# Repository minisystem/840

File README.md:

SYSTEM80 840
======================================

Voltage controlled ADSR in Eurorack format. Currently under development.

Hardware design by Minisystem: info@system80.net

LICENSE
=======
cc by-nc-sa
https://creativecommons.org/licenses/by-nc-sa/4.0/

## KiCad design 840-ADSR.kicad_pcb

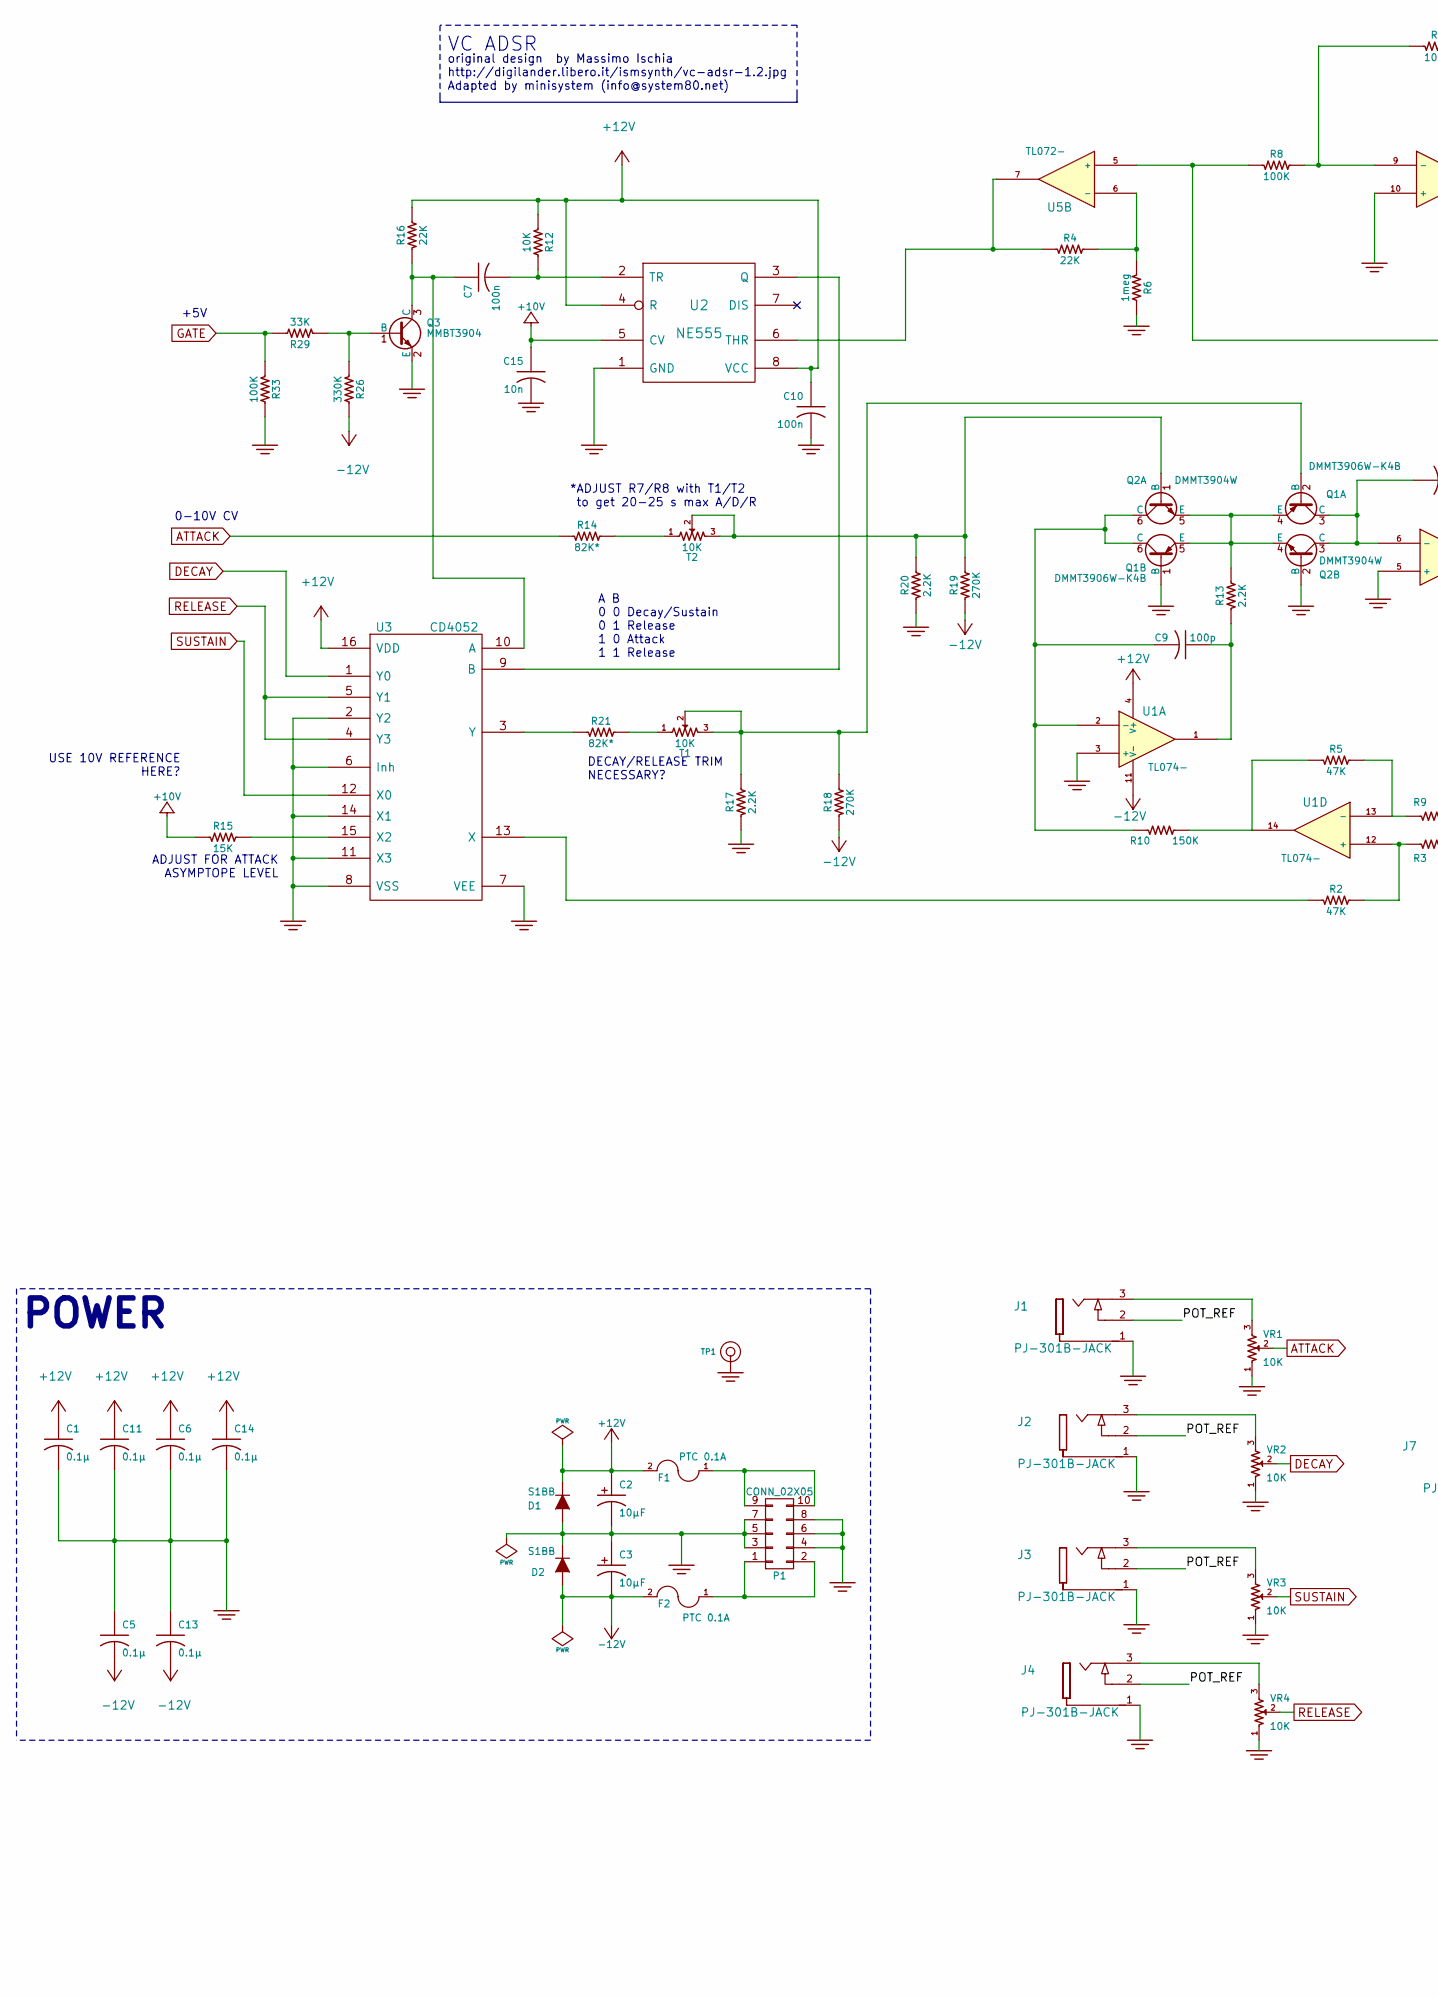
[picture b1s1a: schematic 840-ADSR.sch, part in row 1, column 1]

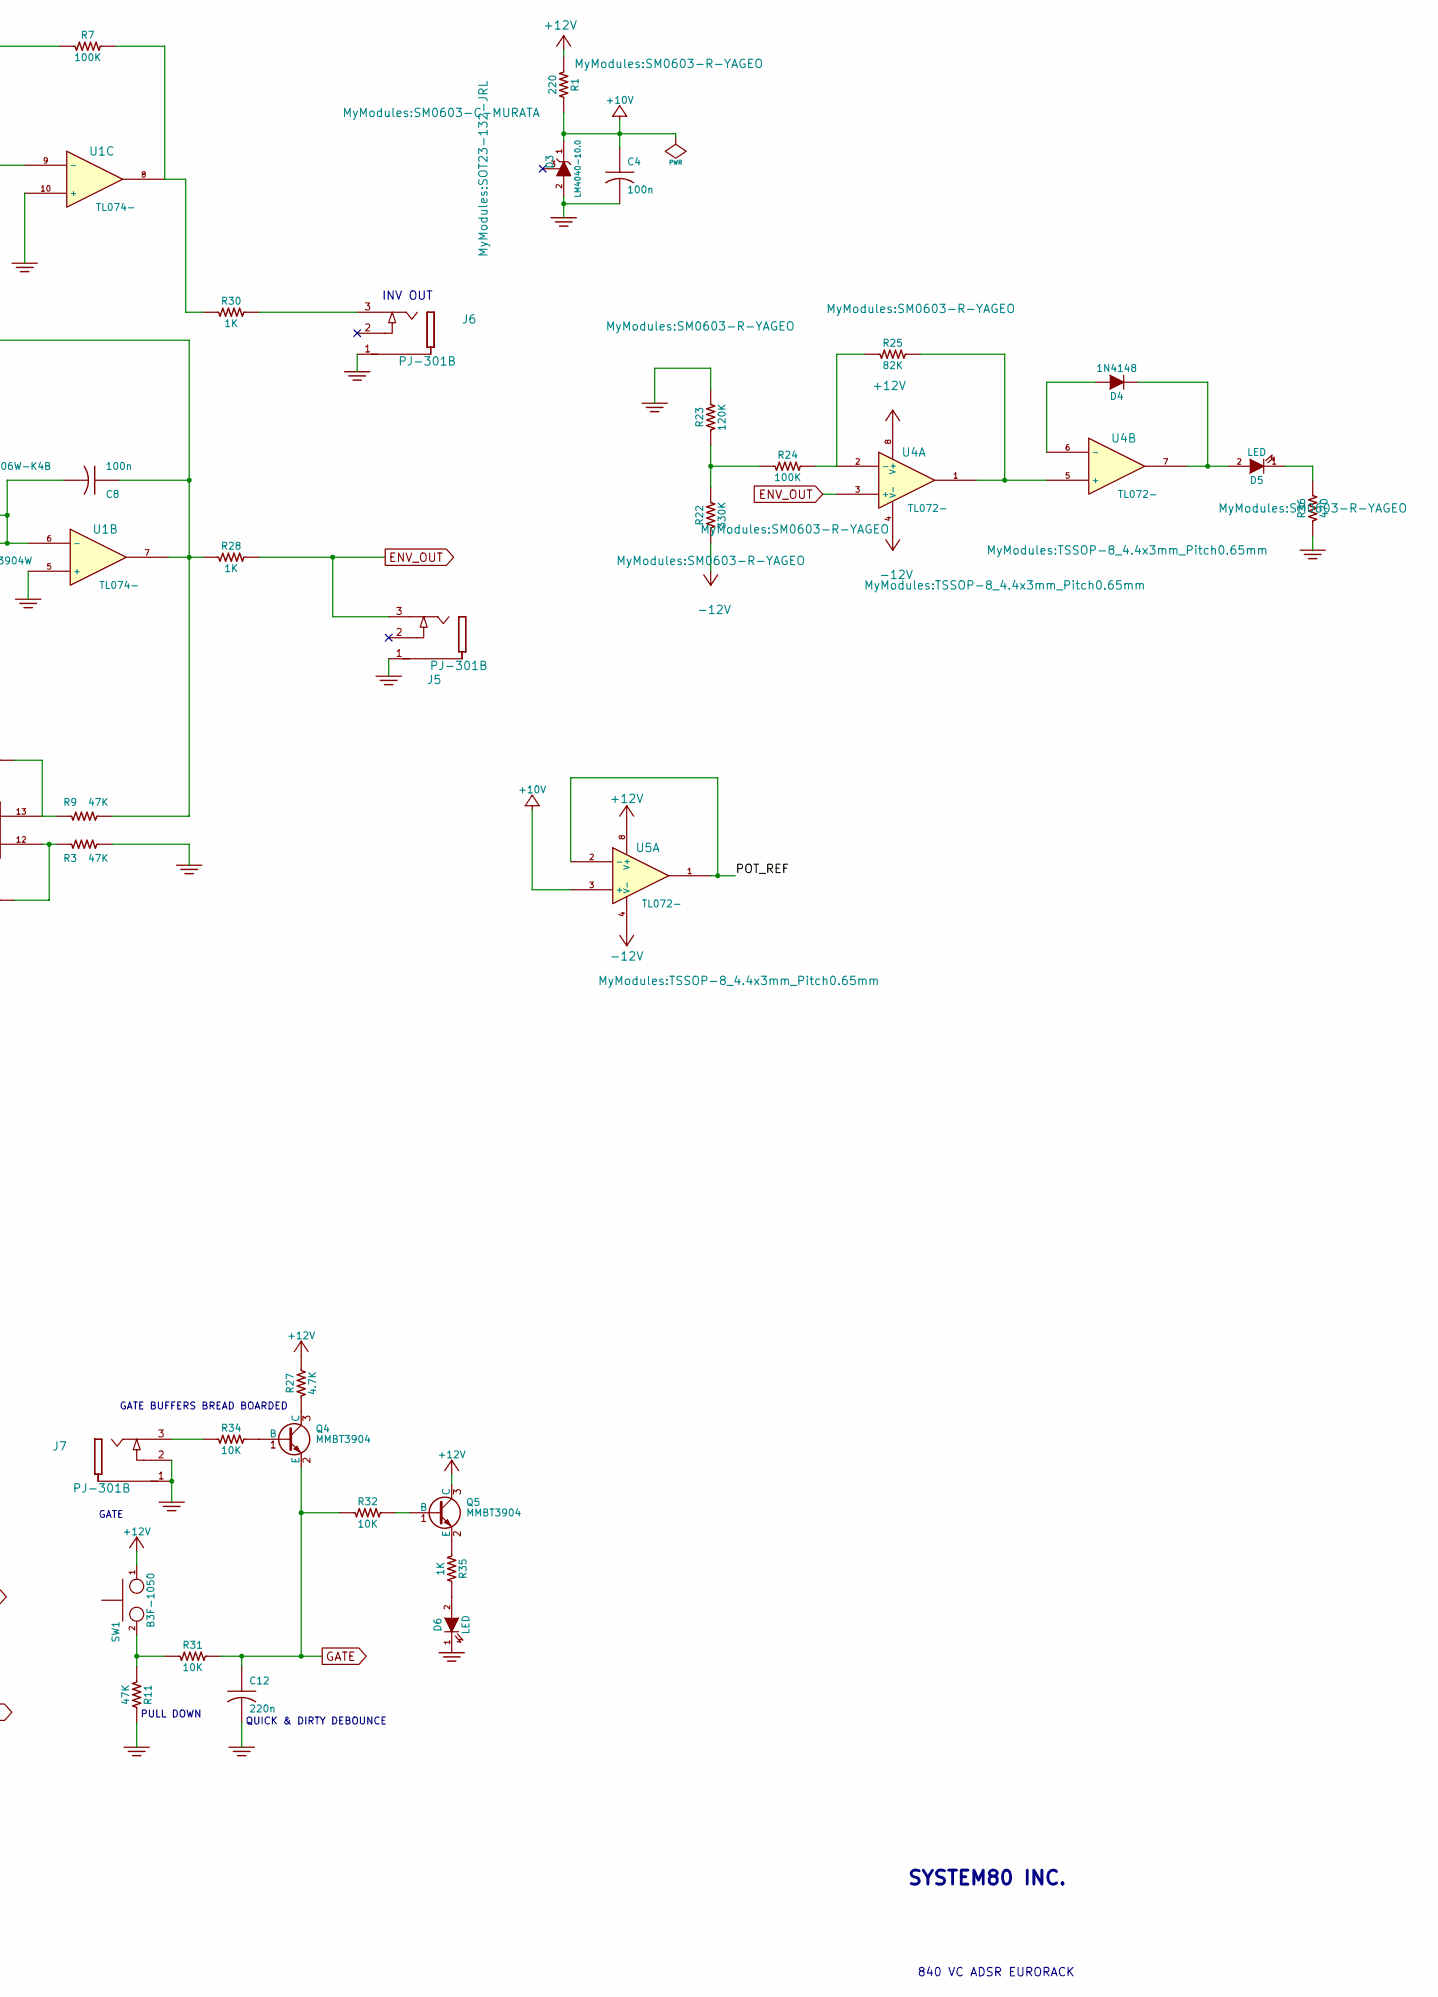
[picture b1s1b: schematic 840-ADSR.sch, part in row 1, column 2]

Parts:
C1, C5, C6, C11, C13, C14: 0.1µ; SM0603-C-MURATA
C2, C3: 10μF; jrl_c_elec_5x5.3
C4, C7, C8, C10: 100n; SM0603-C-MURATA
C9: 100p; SM0603-C-MURATA
C12: 220n; SM0805-HAND
C15: 10n; SM0603-C-MURATA
D1, D2: S1BB; SMB-1C2A
D3: LM4040-10.0; SOT23-132-JRL
D4: 1N4148; SOD323-C1A2
D5, D6: LED; 3MM-LED-C1A2
F1, F2: PTC 0.1A; SM0805-HAND
J1, J2, J3, J4: PJ-301B-JACK; PJ-301B-JACK-SLOTS
J5, J6, J7: PJ-301B; PJ-301B-JACK-SLOTS
P1: CONN_02X05; Pin_Header_Straight_2x05_Pitch2.54mm
Q1: DMMT3906W-K4B; SOT363-JRL
Q2: DMMT3904W; SOT363-JRL
Q3, Q4, Q5: MMBT3904; SOT23-132-JRL
R1: 220; SM0603-R-YAGEO
R2, R3, R5, R9, R11: 47K; SM0603-R-YAGEO
R4, R16: 22K; SM0603-R-YAGEO
R6: 1meg; SM0603-R-YAGEO
R7, R8, R24, R33: 100K; SM0603-R-YAGEO
R10: 150K; SM0603-R-YAGEO
R12, R31, R32, R34: 10K; SM0603-R-YAGEO
R13, R17, R20: 2.2K; SM0603-R-YAGEO
R14, R21: 82K*; SM0603-R-YAGEO
R15: 15K; SM0603-R-YAGEO
R18, R19: 270K; SM0603-R-YAGEO
R22, R26: 330K; SM0603-R-YAGEO
R23: 120K; SM0603-R-YAGEO
R25: 82K; SM0603-R-YAGEO
R27: 4.7K; SM0603-R-YAGEO
R28, R30, R35: 1K; SM0603-R-YAGEO
R29: 33K; SM0603-R-YAGEO
R36: 470; SM0603-R-YAGEO
SW1: B3F-1050; B3F-1050-OMRON
T1, T2: 10K; TC33X-2
TP1: CONN_1; TEST_POINT_LOOP_4592
U1: TL074-; TSSOP-14_4.4x5mm_Pitch0.65mm
U2: NE555; TSSOP-8_4.4x3mm_Pitch0.65mm
U3: CD4052; TSSOP-16_4.4x5mm_Pitch0.65mm_jrl
U4, U5: TL072-; TSSOP-8_4.4x3mm_Pitch0.65mm
VR1, VR2, VR3, VR4: 10K; RD901F-ALPHA-POT-T18

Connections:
+10V: C4.1, C15.1, D3.1 (K), R1.2, R15.1, U2.5 (CV), U5.3 (+)
+12V: C1.1, C2.1 (+), C6.1, C10.1, C11.1, C14.1, D1.1 (K), F1.2, Q5.3 (C), R1.1, R12.1, R16.2, R27.2, SW1.1, U1.4 (V+), U2.4 (R), U2.8 (VCC), U3.16 (VDD), U4.8 (V+), U5.8 (V+)
-12V: C3.2 (-), C5.2, C13.2, D2.2 (A), F2.2, R18.1, R19.1, R22.1, R26.2, U1.11 (V-), U4.4 (V-), U5.4 (V-)
/POT_REF: J1.2, J2.2, J3.2, J4.2, U5.1, U5.2 (-)
ATTACK: R14.1, VR1.2
DECAY: U3.1 (Y0), VR2.2
ENV_OUT: J5.3, R28.2, U4.3 (+)
GATE: C12.1, Q4.2 (E), R29.2, R31.2, R32.1, R33.1
GND: C1.2, C2.2 (-), C3.1 (+), C4.2, C5.1, C6.2, C10.2, C11.2, C12.2, C13.1, C14.2, C15.2, D1.2 (A), D2.1 (K), D3.2 (A), D6.1 (K), J1.1, J2.1, J3.1, J4.1, J5.1, J6.1, J7.1, J7.2, P1.3, P1.4, P1.5, P1.6, P1.7, P1.8, Q1.1 (B), Q2.2 (B), Q3.2 (E), R3.2, R6.2, R11.2, R17.1, R20.1, R23.2, R33.2, R36.1, TP1.1, U1.3 (+), U1.5 (+), U1.10 (+), U2.1 (GND), U3.2 (Y2), U3.6 (Inh), U3.7 (VEE), U3.8 (VSS), U3.11 (X3), U3.14 (X1), VR1.1, VR2.1, VR3.1, VR4.1
unnamed: C7.1, Q3.3 (C), R16.1, U3.10 (A)
unnamed: C7.2, R12.2, U2.2 (TR)
unnamed: C8.1, R8.1, R9.2, R28.1, U1.7, U5.5 (+)
unnamed: C8.2, Q1.3 (C), Q2.3 (C), U1.6 (-)
unnamed: C9.1, R13.1, U1.1
unnamed: C9.2, Q1.6 (C), Q2.6 (C), R10.1, U1.2 (-)
unnamed: D4.1 (K), D5.2 (A), U4.7
unnamed: D4.2 (A), U4.6 (-)
unnamed: D5.1 (K), R36.2
unnamed: D6.2 (A), R35.2
unnamed: F1.1, P1.9, P1.10
unnamed: F2.1, P1.1, P1.2
unnamed: J1.3, VR1.3
unnamed: J2.3, VR2.3
unnamed: J3.3, VR3.3
unnamed: J4.3, VR4.3
unnamed: J6.3, R30.2
unnamed: J7.3, R34.1
unnamed: Q1.2 (B), R17.2, R18.2, T1.2, T1.3
unnamed: Q1.4 (E), Q1.5 (E), Q2.4 (E), Q2.5 (E), R13.2
unnamed: Q2.1 (B), R19.2, R20.2, T2.2, T2.3
unnamed: Q3.1 (B), R26.1, R29.1
unnamed: Q4.1 (B), R34.2
unnamed: Q4.3 (C), R27.1
unnamed: Q5.1 (B), R32.2
unnamed: Q5.2 (E), R35.1
unnamed: R2.1, U3.13 (X)
unnamed: R2.2, R3.1, U1.12 (+)
unnamed: R4.1, U2.6 (THR), U5.7
unnamed: R4.2, R6.1, U5.6 (-)
unnamed: R5.2, R9.1, U1.13 (-)
unnamed: R7.1, R8.2, U1.9 (-)
unnamed: R5.1, R10.2, U1.14
unnamed: R11.1, R31.1, SW1.2
unnamed: R14.2, T2.1
unnamed: R15.2, U3.15 (X2)
unnamed: R21.1, U3.3 (Y)
unnamed: R21.2, T1.1
unnamed: R22.2, R23.1, R24.1
unnamed: R24.2, R25.1, U4.2 (-)
unnamed: R25.2, U4.1, U4.5 (+)
unnamed: R7.2, R30.1, U1.8
unnamed: U2.3 (Q), U3.9 (B)
RELEASE: U3.4 (Y3), U3.5 (Y1), VR4.2
SUSTAIN: U3.12 (X0), VR3.2

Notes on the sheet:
SYSTEM80 INC.
840 VC ADSR EURORACK
*ADJUST R7/R8 with T1/T2 to get 20-25 s max A/D/R
0-10V CV
+5V
VC ADSR
original design by Massimo Ischia http://digilander.libero.it/ismsynth/vc-adsr-1.2.jpg Adapted by minisystem (info@system80.net)
POWER
GATE
GATE BUFFERS BREAD BOARDED
QUICK & DIRTY DEBOUNCE
INV OUT
A B 0 0 Decay/Sustain 0 1 Release 1 0 Attack 1 1 Release
DECAY/RELEASE TRIM NECESSARY?
PULL DOWN
ADJUST FOR ATTACK ASYMPTOPE LEVEL
USE 10V REFERENCE HERE?

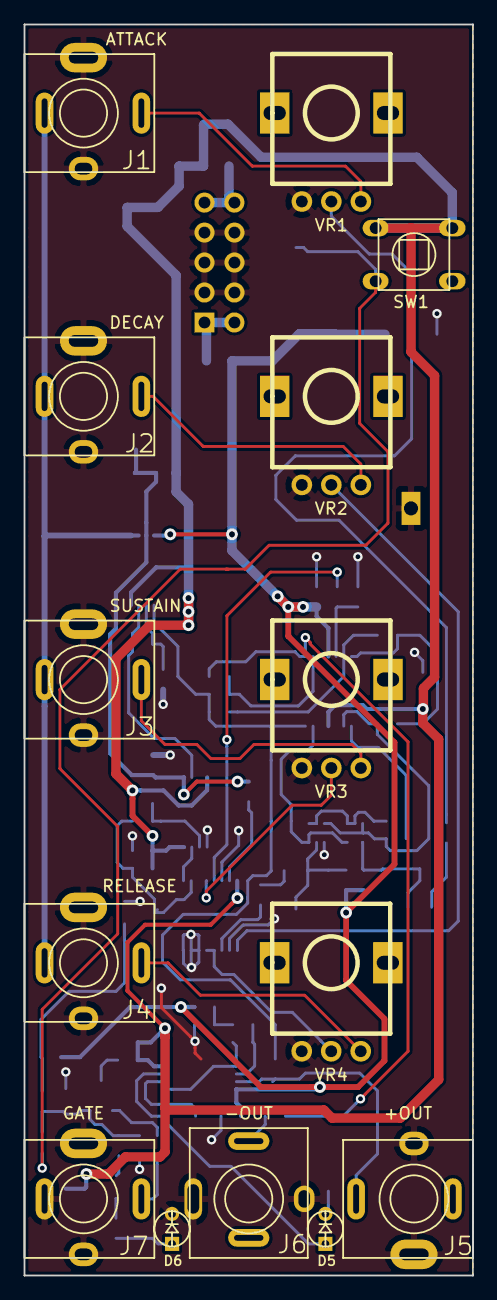
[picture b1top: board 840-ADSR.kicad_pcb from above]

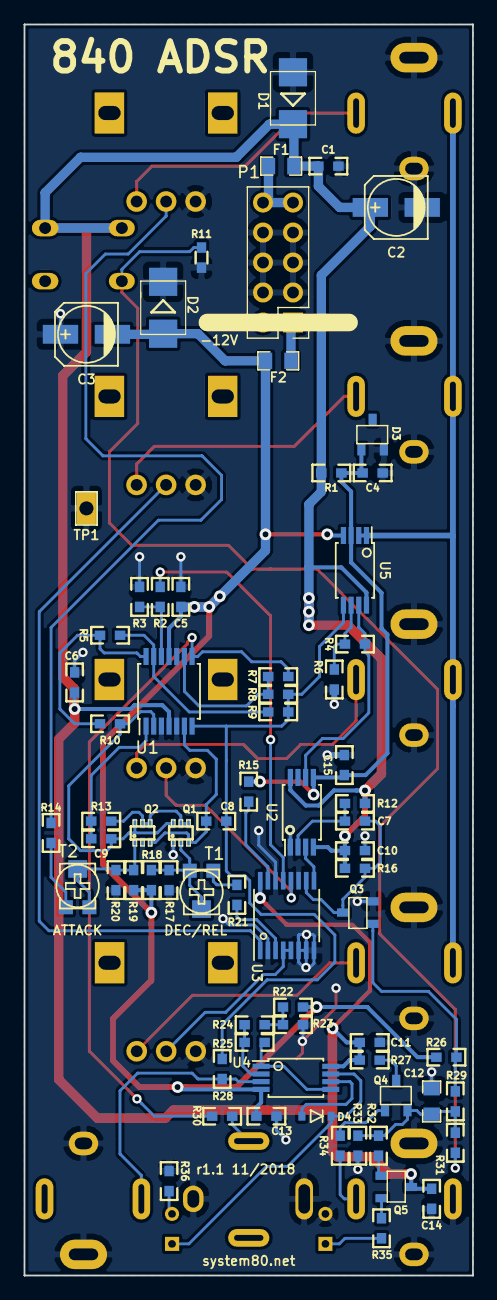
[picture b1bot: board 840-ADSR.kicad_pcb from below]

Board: 2 copper layers, 38.0 x 106.0 mm, 85 parts (71 on the bottom side), 54 nets.

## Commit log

2018-06-19 first commit"
    "
2018-06-19 added readme
2018-06-20 footprints associated, starting placing
2018-06-23 parts mostly placed, starting to route
2018-06-25 almost done routing
2018-06-25 routed, need to place silk screen labels
2018-06-26 added .gitignore and some silk screen tweaking
2018-06-28 bit of rail tweaking
2018-07-18 delted 3.3K resistor connected to 555 CV pin and replaced wtih 10V reference. duh.
2018-11-03 prototype built, needs tweaking, about to start
2018-11-05 v1.1 in the works. buffered env output to 555 threshold input, changed 10V reference distribution added some notes
